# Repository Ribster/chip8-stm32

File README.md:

CHIP 8 emulator
==========

STM32 based emulator with chip8 virtual machine.

Dirs
==========
tools/	dir with conwerter of image in propertly format
mcu/	program writen to mcu (Eclipse progect)
pcb/	schematics and pcb ready to laser printer production (Eagle)

How to repeat
==========

1. Product pcb
2. SMT components
3. Compile or use prebuild hex/elf files to write in mcu
4. Enjoy

TODO
==========
1. Transfer to new random generator
2. Add button patterns to game (now button worked propertly only in tetris)
3. Add to disign Beeper 
4. Redisign schematics
5. Create case for console

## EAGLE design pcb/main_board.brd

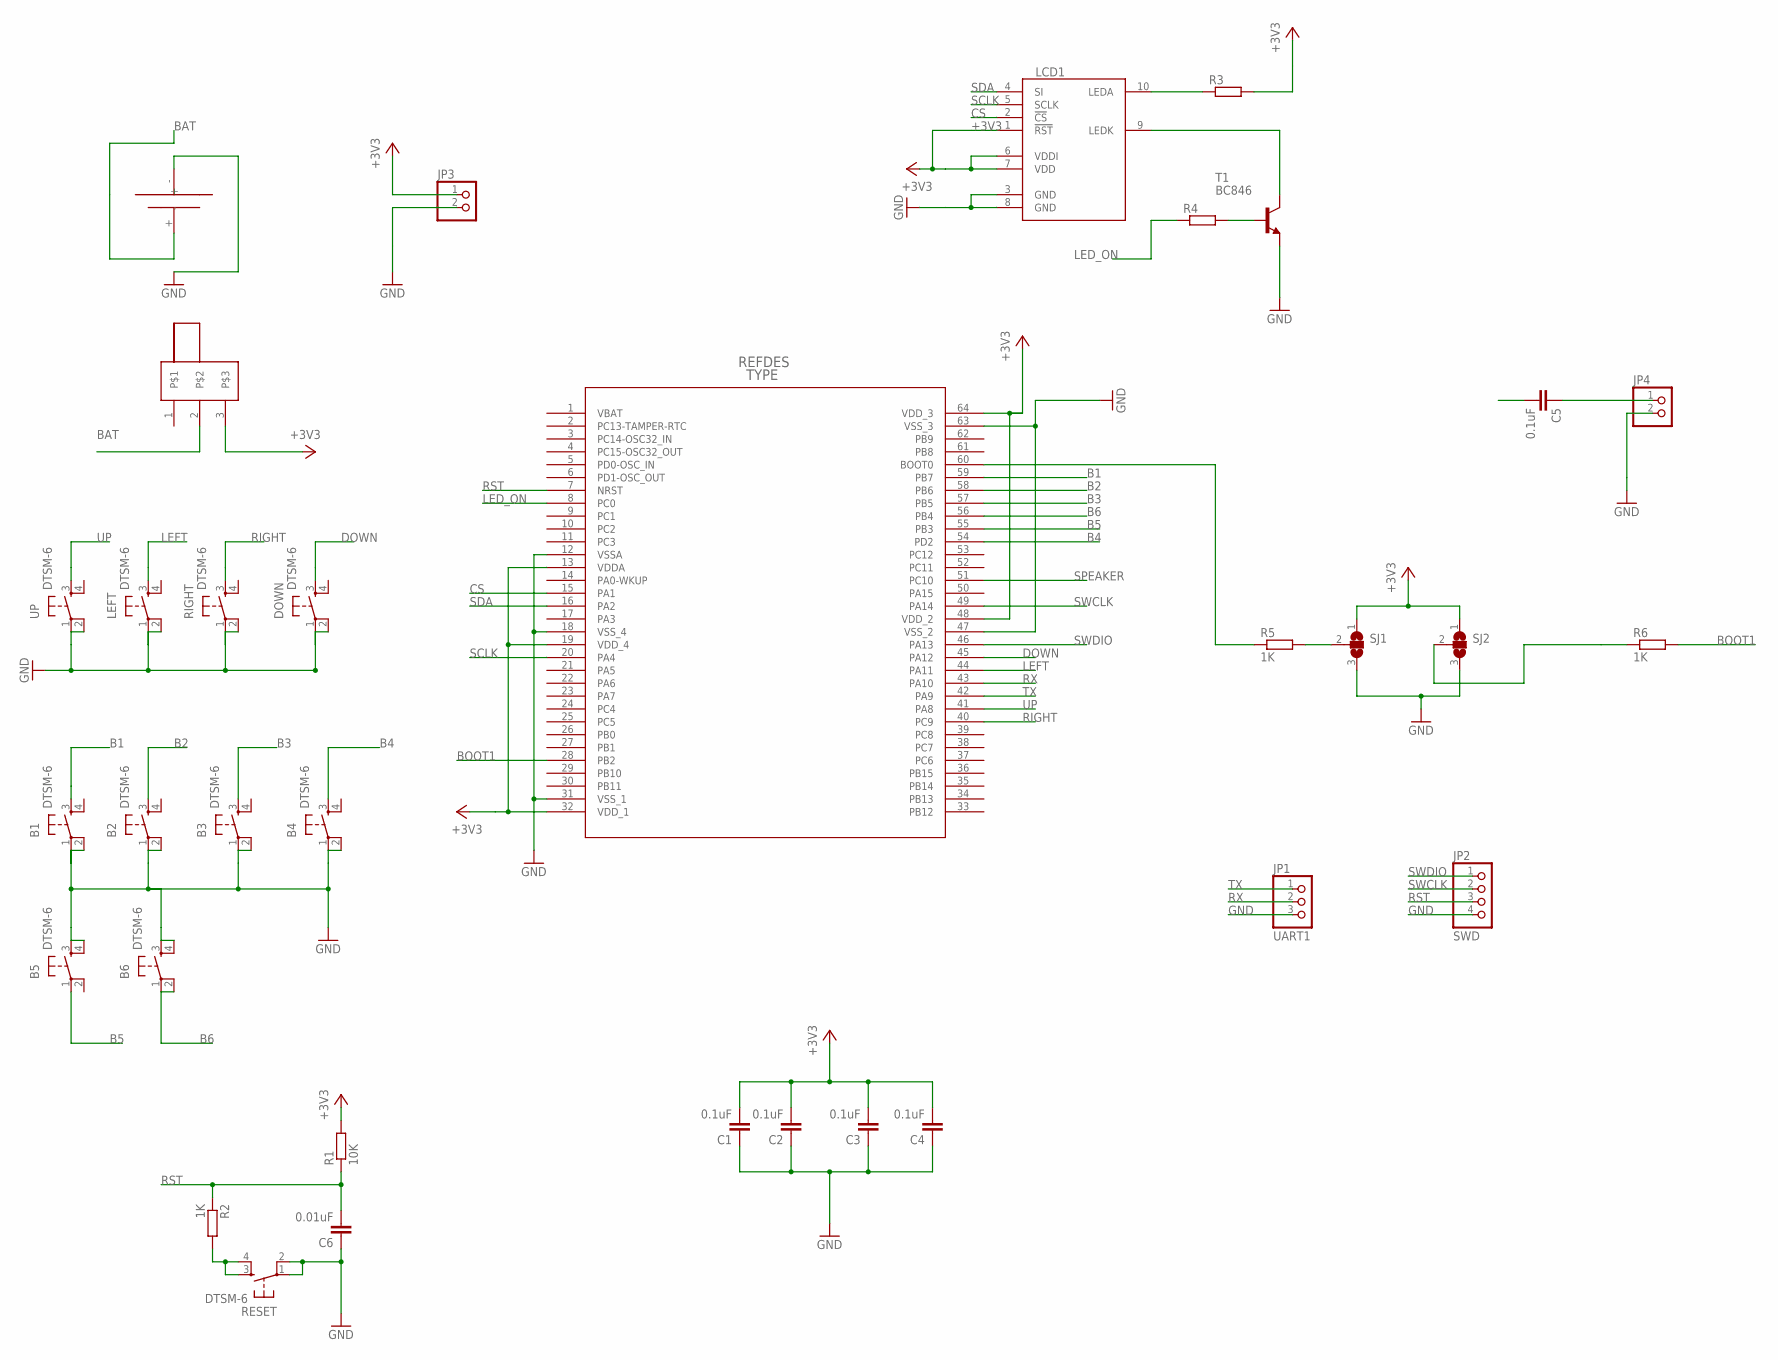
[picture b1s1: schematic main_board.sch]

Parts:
B1, B2, B3, B4, B5, B6: DTSM-6
C1, C2, C3, C4, C5: 0.1uF; C1206
C6: 0.01uF; C1206
DOWN: DTSM-6
JP1: UART1; 1X03/90
JP2: SWD; 1X04/90
JP3, JP4: PINHD-1X2; 1X02
LCD1: LCD1202; NOKIA1202LCD
LEFT: DTSM-6
R1: 10K; R1206
R2, R5, R6: 1K; R1206
R3, R4: R-EU_R1206; R1206
RESET: DTSM-6
RIGHT: DTSM-6
SJ1, SJ2: SJ2W; SJ_2
T1: BC846; SOT23
U$1: STM32F100RBT6B; LQFP-64
U$2: BAT33; 3V3BATPACK
U$3: SWITCH3
UP: DTSM-6

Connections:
+3V3: C1.2, C2.2, C3.2, C4.2, JP3.1, LCD1.1 (!RST), LCD1.6 (VDDI), LCD1.7 (VDD), R1.2, R3.2, SJ1.1, SJ2.1, U$1.13 (VDDA), U$1.19 (VDD_4), U$1.32 (VDD_1), U$1.48 (VDD_2), U$1.64 (VDD_3), U$3.3
B1: B1.3, U$1.59 (PB7)
B2: B2.3, U$1.58 (PB6)
B3: B3.3, U$1.57 (PB5)
B4: B4.3, U$1.54 (PD2)
B5: B5.1, U$1.55 (PB3)
B6: B6.1, B6.2, U$1.56 (PB4)
BAT: U$2.+, U$3.2
BOOT1: R6.2, U$1.28 (PB2)
CS: LCD1.2 (!CS), U$1.15 (PA1)
DOWN: DOWN.3, U$1.45 (PA12)
GND: B1.1, B1.2, B2.1, B2.2, B3.1, B3.2, B4.1, B4.2, B5.3, B5.4, B6.3, B6.4, C1.1, C2.1, C3.1, C4.1, C6.1, DOWN.1, DOWN.2, JP1.3, JP2.4, JP3.2, JP4.2, LCD1.3 (GND), LCD1.8 (GND), LEFT.1, LEFT.2, RESET.1, RESET.2, RIGHT.1, RIGHT.2, SJ1.3, SJ2.3, T1.2 (E), U$1.12 (VSSA), U$1.18 (VSS_4), U$1.31 (VSS_1), U$1.47 (VSS_2), U$1.63 (VSS_3), U$2.-, UP.1, UP.2
LED_ON: R4.1, U$1.8 (PC0)
LEFT: LEFT.3, U$1.44 (PA11)
unnamed: LCD1.9 (LEDK), T1.3 (C)
unnamed: R4.2, T1.1 (B)
unnamed: R2.2, RESET.3, RESET.4
unnamed: LCD1.10 (LEDA), R3.1
unnamed: R5.1, U$1.60 (BOOT0)
unnamed: R5.2, SJ1.2
unnamed: C5.1, JP4.1
unnamed: R6.1, SJ2.2
RIGHT: RIGHT.3, U$1.40 (PC9)
RST: C6.2, JP2.3, R1.1, R2.1, U$1.7 (NRST)
RX: JP1.2, U$1.43 (PA10)
SCLK: LCD1.5 (SCLK), U$1.20 (PA4)
SDA: LCD1.4 (SI), U$1.16 (PA2)
SPEAKER: C5.2, U$1.51 (PC10)
SWCLK: JP2.2, U$1.49 (PA14)
SWDIO: JP2.1, U$1.46 (PA13)
TX: JP1.1, U$1.42 (PA9)
UP: U$1.41 (PA8), UP.3

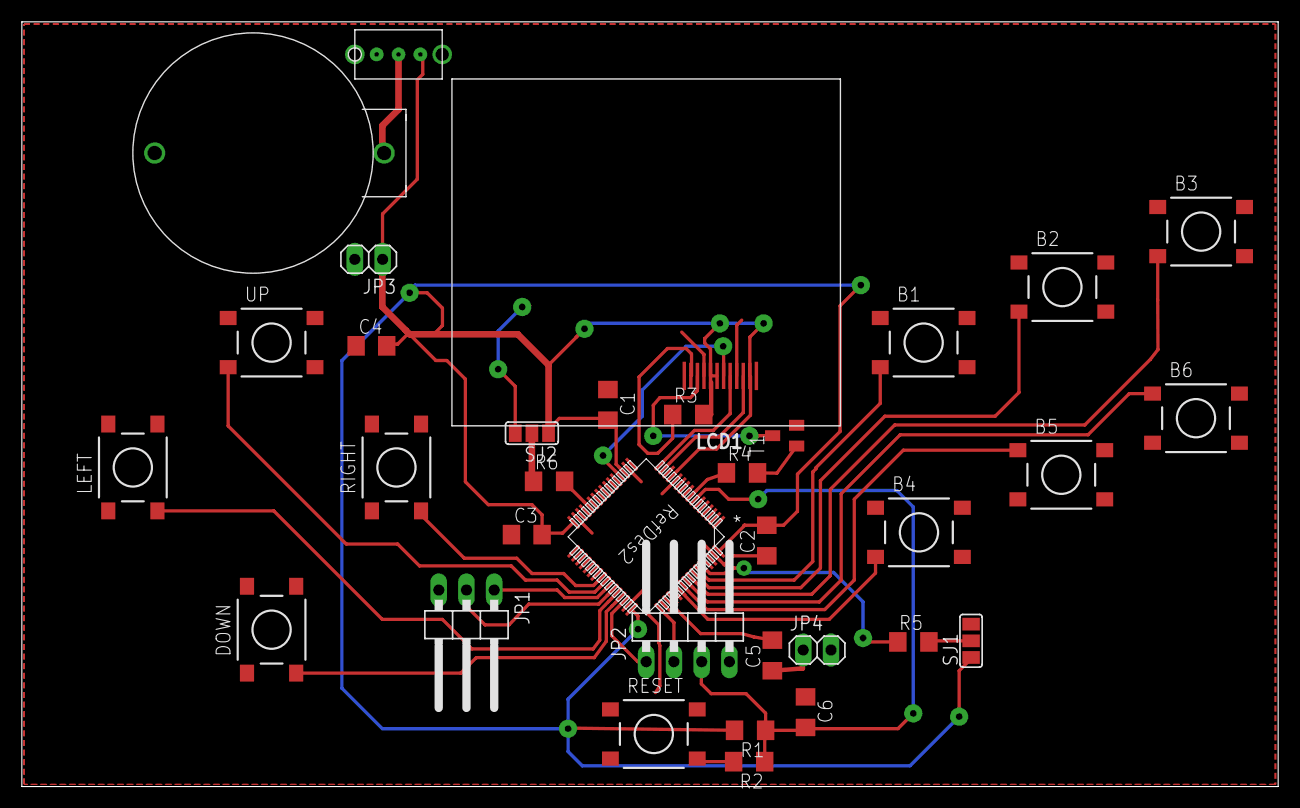
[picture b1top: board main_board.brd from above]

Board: 2 copper layers, 115.0 x 70.0 mm, 34 parts (0 on the bottom side), 32 nets.

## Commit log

2014-08-28 Add file tree and schematics file
2014-08-28 Eclipse project for emulator
2014-08-29 Add egg and on/off backlight. +hex/rlf file add for upload to mcu withou compile
2014-08-29 Fix gitignore
2014-09-06 Release 1.0a
